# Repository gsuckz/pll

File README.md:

# Sintetizador de Frecuencias en banda Ku 

## Funcionamiento
    El dispositivo genera una señal en banda Ku {10,6 , 11,8} GHz. Con un paso de 1Mhz, teniendo 1200 Valores posibles. Estos se envían a través de una aplicacion de Android usando Bluetooth. También es posible realizar un barrido de frecuecnias, con un paso menor, 0,25 MHz.

Este repositorio contiene el código para controlar un Sintentizador de frecuencias Zarlink SP5769 que controla un VCO HMC534LP5.

La dirección I2C del SP5769 se selecciona con el nivel del tension aplicado a ADDRESS (%Vcc) ADDRESS = "11000101"

El ESP32 debe escribir en los registros del SP5769 los valores (a través de un bus I2C). Los registros son:
## Programmable divider: 
    Controla la razón entre la frecuencia del VCO interno y la de referencia (Un numero de 15 bit)
## Control Data: Tiene varios bits que controlan el funcionamiento (Ver datasheet para saber posicion):

    [R3:R0]: Controla el divisor de frecuencia de referencia (Ver tabla) - Ajustado al valor 64 -> 0101

    [C1:C0]: Seleccion la corriente de la bomba de carga. Ver tabla datasheet (Valor fijado por el circuito)

    RE: Enable del oscilador de ref 

    [T2:T0] = Bits de control de modo test - No se usa

    [P3:P0] = Estados del puerto de salida - No se usa

    RS: REF/COMP seleccion (Se usa alta impedancia)

Aquí se configura: Modo Test Off, Corriente de la bomba de carga Icp=+-155[µA], pin
de REF/COMP en alta impedancia, y todos los puertos, P3 a P0 a 0[V]

## Especifaciones del programa 
### Iniciar 
    El programa debe iniciar la comunicación por bluetooth y configurar el registro de control según se indica en el documento "INFORME-TRABAJO-GRADUACION-CANGEMI-JOSE-I.pdf". Luego debe esperar por cualquiera de las 2 instrucciones posibles.

### Ajuste de frecuencia
    El programa debe recibir por bluetooth el valor de la frecuncia deseada, luego debe calcular el valor del multiplicador necesario y escribirlo en los registros programmable divider.

### Barrido de frecuencia
    El programa de barrer las frecuencias sintetizables en un tiempo indicado por el usuario. Con limites Tmin y Tmax

El valor recibido es una cadena de caracteres con la frecuencia

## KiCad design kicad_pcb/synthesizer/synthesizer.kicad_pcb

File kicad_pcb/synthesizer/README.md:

# Sintetizador

- Transistor BCW31 : [datasheet_BCW31](https://www.alldatasheet.es/datasheet-pdf/view/16150/PHILIPS/BCW31.html)
- Conector SMA Chasis: [Datasheet_Sma](https://www.snapeda.com/parts/CONSMA006.062-G/TE%20Connectivity/datasheet/)

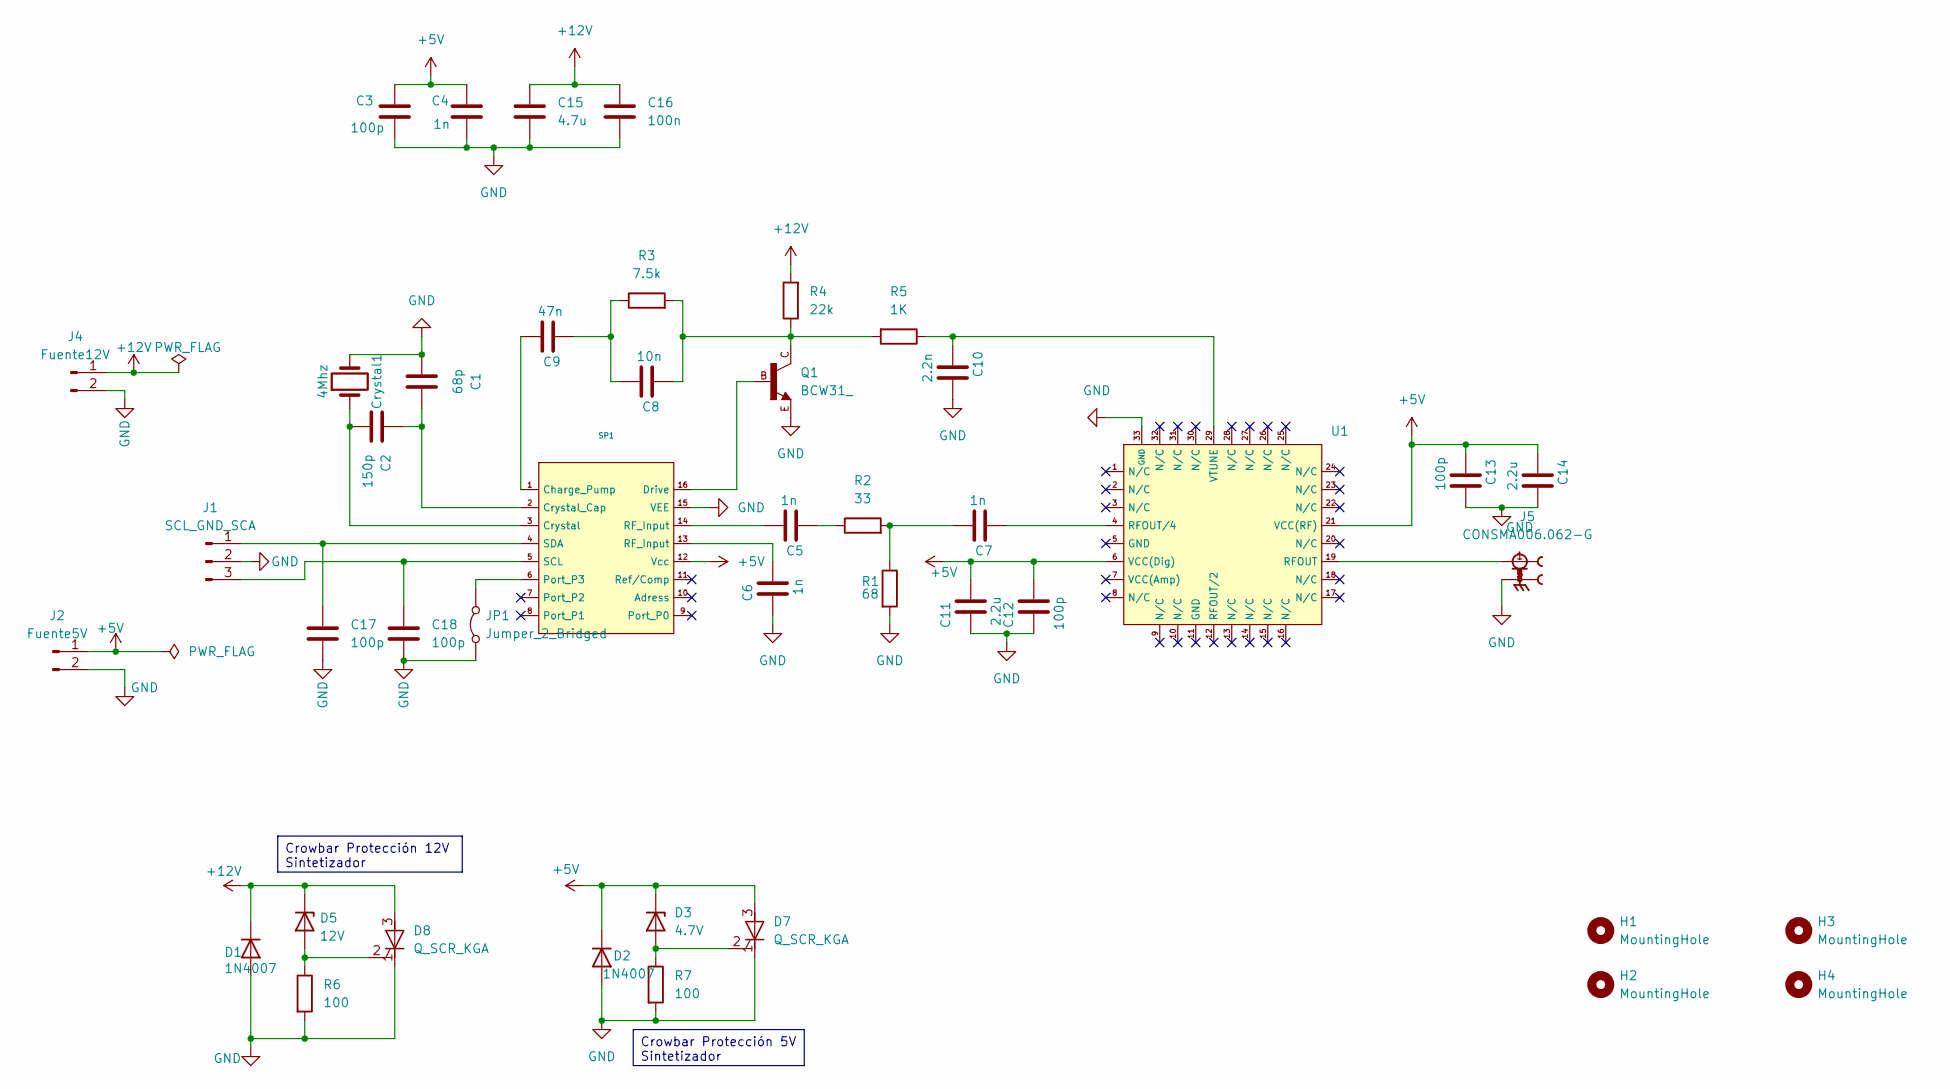
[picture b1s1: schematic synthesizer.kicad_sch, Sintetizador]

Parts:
C1: 68p; C_0805_2012Metric_Pad1.18x1.45mm_HandSolder
C2: 150p; C_0805_2012Metric_Pad1.18x1.45mm_HandSolder
C3, C12, C13, C17, C18: 100p; C_0805_2012Metric_Pad1.18x1.45mm_HandSolder
C4, C5, C6, C7: 1n; C_0805_2012Metric_Pad1.18x1.45mm_HandSolder
C8: 10n; C_0805_2012Metric_Pad1.18x1.45mm_HandSolder
C9: 47n; C_0805_2012Metric_Pad1.18x1.45mm_HandSolder
C10: 2.2n; C_0805_2012Metric_Pad1.18x1.45mm_HandSolder
C11, C14: 2.2u; C_0805_2012Metric_Pad1.18x1.45mm_HandSolder
C15: 4.7u; CP_Radial_D8.0mm_P3.80mm
C16: 100n; C_0805_2012Metric_Pad1.18x1.45mm_HandSolder
Crystal1: 4Mhz; Crystal_HC18-U_Vertical
D1, D2: 1N4007; D_DO-41_SOD81_P10.16mm_Horizontal
D3: 4.7V; D_DO-41_SOD81_P10.16mm_Horizontal
D5: 12V; D_DO-41_SOD81_P10.16mm_Horizontal
D7: Q_SCR_KGA; TO-92_Wide
D8: Q_SCR_KGA; TO-92L_Wide
H1, H2, H3, H4: MountingHole; MountingHole_3.2mm_M3
J1: SCL_GND_SCA; PinHeader_1x03_P2.54mm_Vertical
J2: Fuente5V; PinHeader_1x02_P2.54mm_Vertical
J4: Fuente12V; PinHeader_1x02_P2.54mm_Vertical
J5: CONSMA006.062-G; TE_CONSMA006.062-G; PARTREV B
JP1: Jumper_2_Bridged; PinHeader_1x02_P2.54mm_Vertical
Q1: BCW31_; SOT23-BEC
R1: 68; R_0805_2012Metric_Pad1.20x1.40mm_HandSolder
R2: 33; R_0805_2012Metric_Pad1.20x1.40mm_HandSolder
R3: 7.5k; R_0805_2012Metric_Pad1.20x1.40mm_HandSolder
R4: 22k; R_0805_2012Metric_Pad1.20x1.40mm_HandSolder
R5: 1K; R_0805_2012Metric_Pad1.20x1.40mm_HandSolder
R6, R7: 100; R_Axial_DIN0207_L6.3mm_D2.5mm_P10.16mm_Horizontal
SP1: SOP-16_4.4x10.4mm_P1.27mm
U1: QFN50P500X500X100-33N

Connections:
+5V: C3.1, C4.1, C11.2, C12.2, C13.1, C14.1, D2.1 (K), D3.1 (K), D7.3 (A), J2.1, SP1.12 (Vcc), U1.6 (VCC(Dig)), U1.21 (VCC(RF))
+12V: C15.1, C16.1, D1.1 (K), D5.1 (K), D8.3 (A), J4.1, R4.2
GND: C1.1, C3.2, C4.2, C6.1, C10.2, C11.1, C12.1, C13.2, C14.2, C15.2, C16.2, C17.2, C18.2, Crystal1.2, D1.2 (A), D2.2 (A), D7.1 (K), D8.1 (K), J1.2, J2.2, J4.2, J5.2, J5.3, J5.4, J5.5, JP1.1 (A), Q1.E, R1.2, R6.2, R7.2, SP1.15 (VEE), U1.33 (GND)
unnamed: C5.1, R2.1
unnamed: C5.2, SP1.14 (RF_Input)
unnamed: C6.2, SP1.13 (RF_Input)
unnamed: C7.2, R1.1, R2.2
unnamed: C8.1, Q1.C, R3.2, R4.1, R5.2
unnamed: C8.2, C9.1, R3.1
unnamed: D3.2 (A), D7.2 (G), R7.1
unnamed: D5.2 (A), D8.2 (G), R6.1
unnamed: C17.1, J1.1, SP1.4 (SDA)
unnamed: C18.1, J1.3, SP1.5 (SCL)
unnamed: JP1.2 (B), SP1.6 (Port_P3)
unnamed: C9.2, SP1.1 (Charge_Pump)
unnamed: C2.2, Crystal1.1, SP1.3 (Crystal)
unnamed: C1.2, C2.1, SP1.2 (Crystal_Cap)
unnamed: Q1.B, SP1.16 (Drive)
unnamed: J5.1, U1.19 (RFOUT)
unnamed: C7.1, U1.4 (RFOUT/4)
unnamed: C10.1, R5.1, U1.29 (VTUNE)

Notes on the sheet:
Crowbar Protección 5V Sintetizador
Crowbar Protección 12V Sintetizador

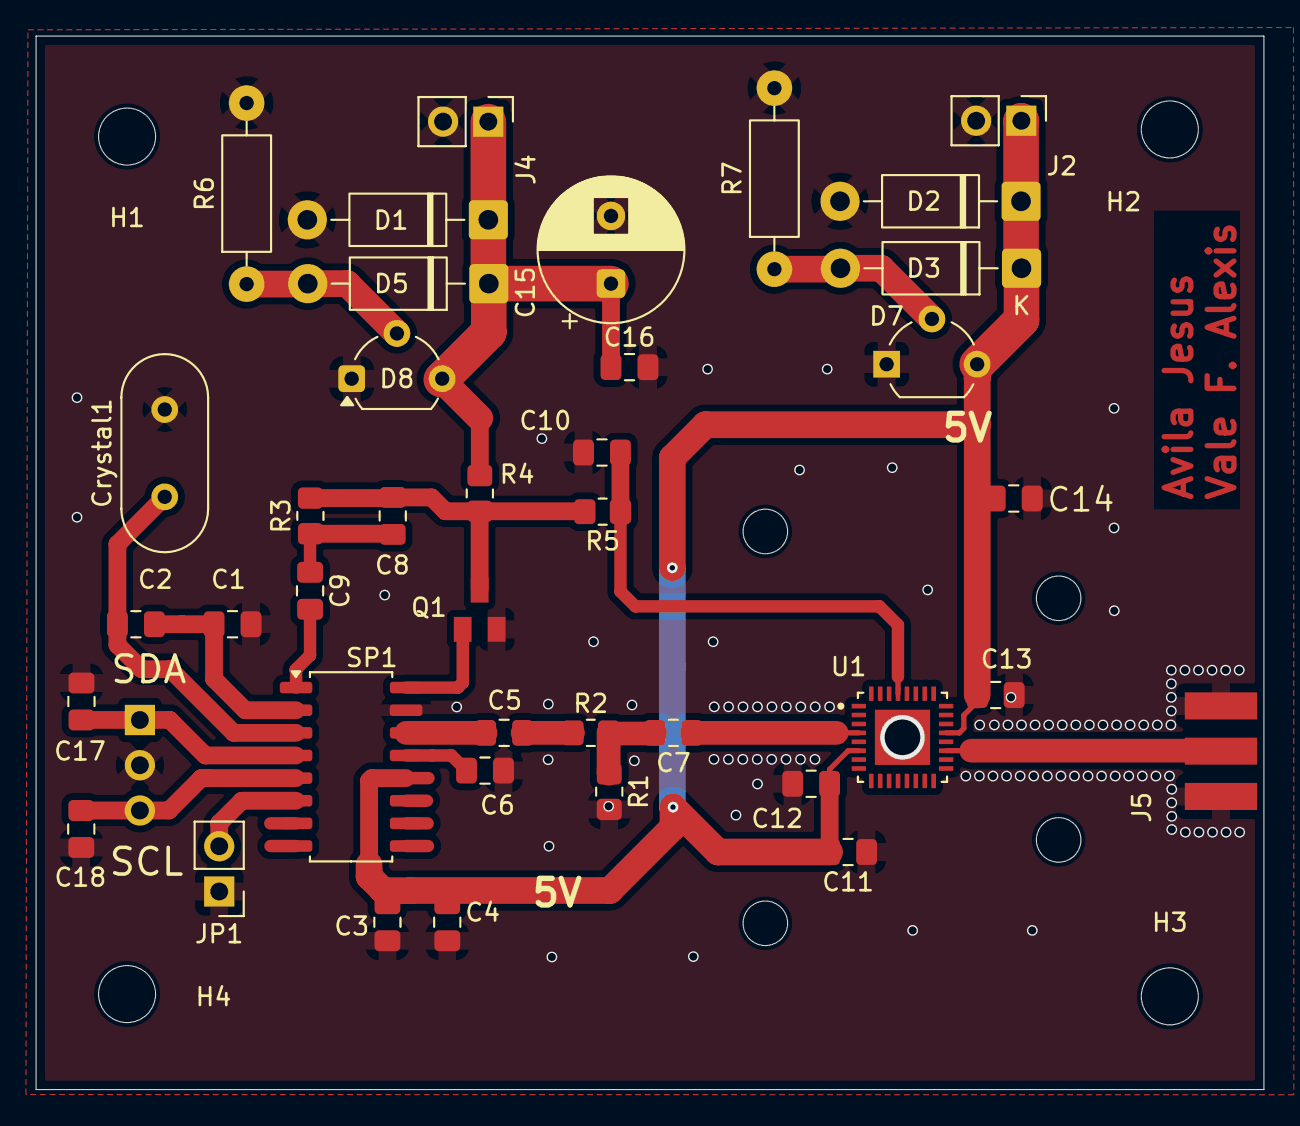
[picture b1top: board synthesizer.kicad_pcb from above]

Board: 2 copper layers, 68.9 x 59.1 mm, 48 parts (1 on the bottom side), 21 nets.

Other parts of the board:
H5, H5#2, H5#3, H5#4: MountingHole; MountingHole_2.5mm

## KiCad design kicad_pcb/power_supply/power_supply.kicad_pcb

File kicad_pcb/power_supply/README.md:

## Datasheet Componentes
- VCO HMC534LP5: [Datasheet](https://www.analog.com/media/en/technical-documentation/data-sheets/hmc534.pdf)

- Sintetizador SP5769: [Datasheet](https://www.alldatasheet.com/datasheet-pdf/view/77217/MITEL/SP5769.html)

- Diodo Zener 1N4732A (4.7V): [Datasheet](https://www.alldatasheet.com/datasheet-pdf/view/58834/DIODES/1N4733A.html) 

- Diodo Zener BZX55C12 (12V): [Datasheet](https://www.vishay.com/docs/85604/bzx55.pdf)

- Tiristor MCR100-6 : [Dataset](https://www.alldatasheet.com/datasheet-pdf/view/888541/SEMTECH_ELEC/MCR100-6.html)

- Tiristor TYN615 (SCR): [Datasheet](https://www.alldatasheet.es/datasheet-pdf/view/25111/STMICROELECTRONICS/TYN612.html)

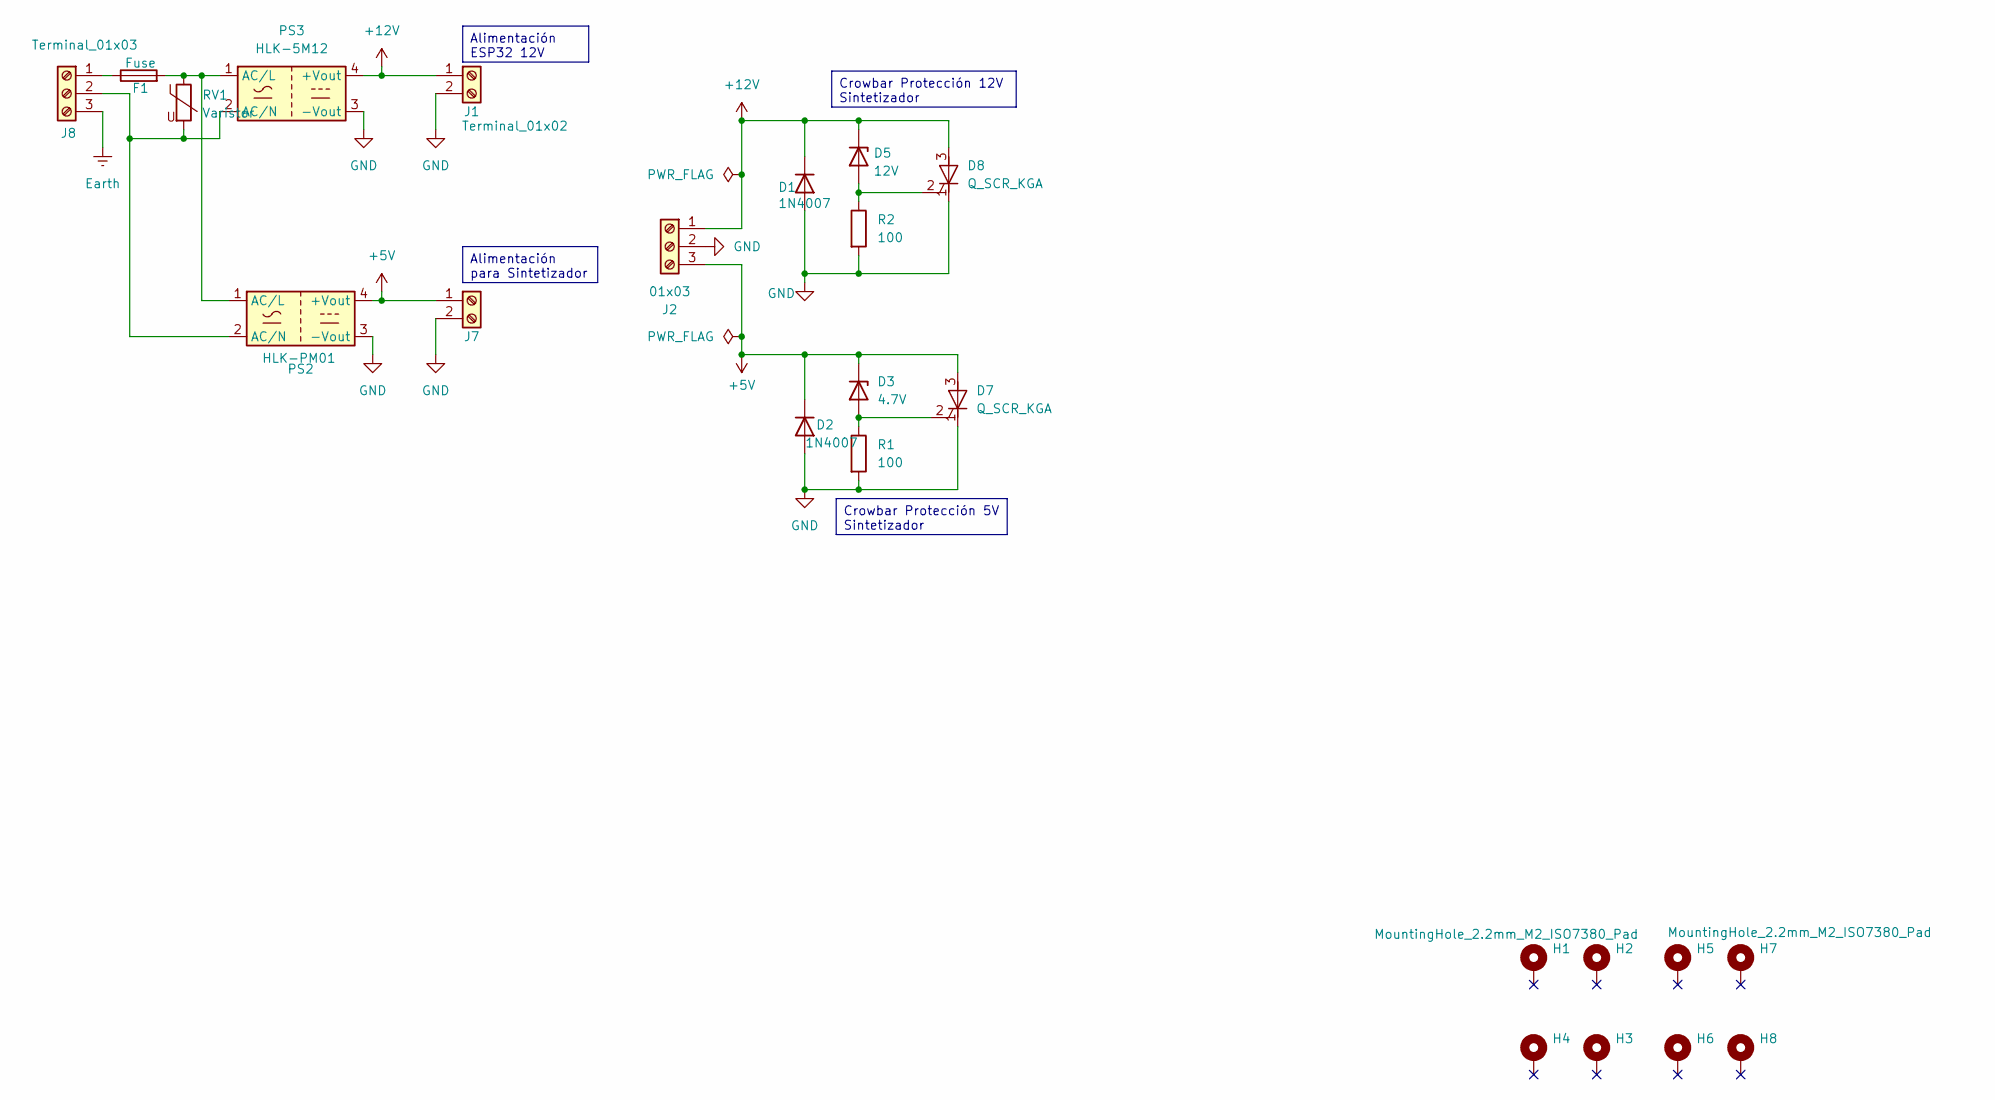
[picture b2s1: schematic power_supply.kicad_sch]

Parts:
D1, D2: 1N4007; D_DO-41_SOD81_P10.16mm_Horizontal
D3: 4.7V; D_DO-41_SOD81_P10.16mm_Horizontal
D5: 12V; D_DO-41_SOD81_P10.16mm_Horizontal
D7: Q_SCR_KGA; TO-92_Wide
D8: Q_SCR_KGA; TO-92L_Wide
F1: Fuse; Fuseholder_Cylinder-5x20mm_Schurter_0031_8201_Horizontal_Op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
H1, H2, H3, H4, H5, H6, H7, H8: MountingHole_2.2mm_M2_ISO7380_Pad
J1, J7: Terminal_01x02; TerminalBlock_MetzConnect_Type011_RT05502HBLC_1x02_P5.00mm_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
J2: 01x03; TerminalBlock_MaiXu_MX126-5.0-03P_1x03_P5.00mm
J8: Terminal_01x03; TerminalBlock_MaiXu_MX126-5.0-03P_1x03_P5.00mm
PS2: HLK-PM01; Converter_ACDC_Hi-Link_HLK-PMxx
PS3: HLK-5M12; Converter_ACDC_Hi-Link_HLK-5Mxx
R1, R2: 100; R_Axial_DIN0207_L6.3mm_D2.5mm_P10.16mm_Horizontal
RV1: Varistor; RV_Disc_D12mm_W4.2mm_P7.5mm

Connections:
+5V: D2.1 (K), D3.1 (K), D7.3 (A), J2.3, J7.1, PS2.4 (+Vout)
+12V: D1.1 (K), D5.1 (K), D8.3 (A), J1.1, J2.1, PS3.4 (+Vout)
Earth: J8.3
GND: D1.2 (A), D2.2 (A), D7.1 (K), D8.1 (K), J1.2, J2.2, J7.2, PS2.3 (-Vout), PS3.3 (-Vout), R1.2, R2.2
unnamed: D3.2 (A), D7.2 (G), R1.1
unnamed: D5.2 (A), D8.2 (G), R2.1
unnamed: F1.1, J8.1
unnamed: J8.2, PS2.2 (AC/N), PS3.2 (AC/N), RV1.2
unnamed: F1.2, PS2.1 (AC/L), PS3.1 (AC/L), RV1.1

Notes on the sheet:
Crowbar Protección 5V Sintetizador
Alimentación para Sintetizador
Crowbar Protección 12V Sintetizador
Alimentación ESP32 12V

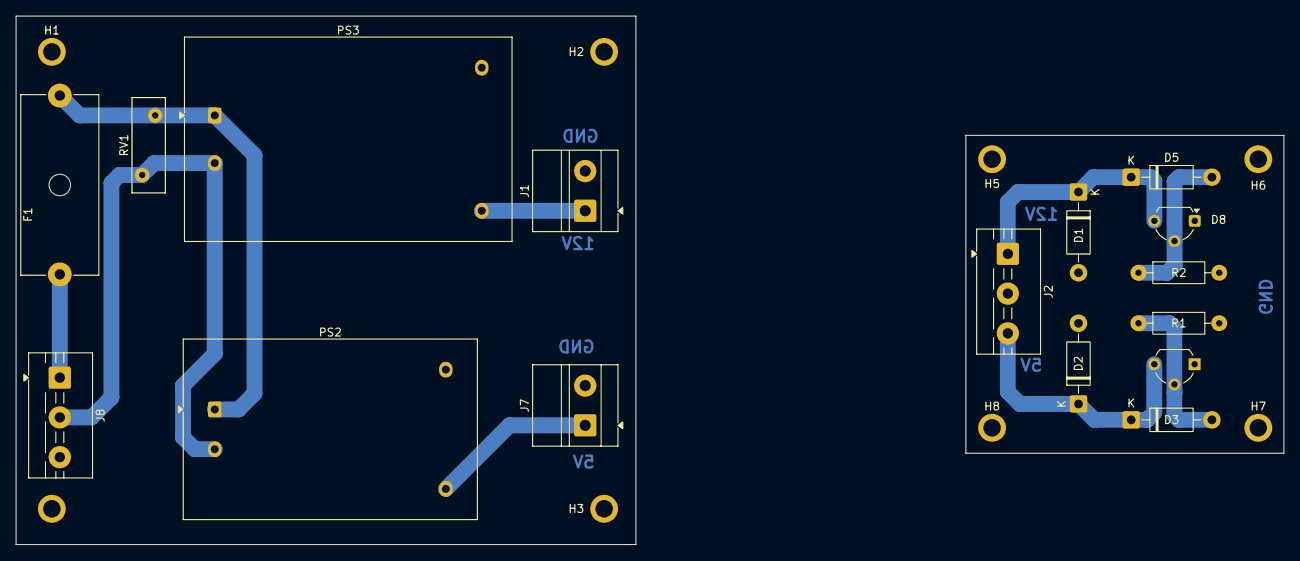
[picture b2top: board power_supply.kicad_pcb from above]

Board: 2 copper layers, 159.5 x 66.5 mm, 24 parts (1 on the bottom side), 8 nets.

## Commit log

2024-08-19 Primer commit
2024-08-19 Actualizado Readme
2024-08-23 Prueba placa OK
2024-08-23 Especificaciones
2024-08-26 COMANDOS FUNCIONA
2024-08-26 Cambios parciales
2024-08-28 Errores de com
2024-08-29 Corregida direccion i2c
2024-10-23 Cambio de valor de R
2024-10-30 agregados test
2024-10-30 agregados msj de test
2024-11-01 nueva modificacion en las divisiones, se agregaron tablas, los divisires estaban mal configurados
2024-11-28 Agregado Display y botones (probar)
2024-11-28 cambios
2025-04-01 Agregado Menu Alexis
2025-04-15 Filtro Botones
2025-04-16 Filtro Anda
2025-05-09 Cambiobot
2025-05-10 Configuración de clangformat. Documentación en buffer
2025-05-10 Separacion Modulo Sint
2025-05-21 App BT anda
2025-06-04 Agregado Barre nfunciona
2025-06-05 Agregado Comando barrer
2025-06-06 SintetizadorTick
2025-06-10 TareaPeriodica
2025-06-12 agregadorBuffer
2025-06-17 AgregadoBarrido2
2025-06-18 Cambios para Tarea
2025-06-18 cambiosprof
2025-06-24 limpieza de codigo sint
2025-06-24 Corregido problema de lock
2025-08-22 NuevaInt
2025-08-22 Pantalla Funciona
2025-08-28 intTeclado
2025-09-01 UI teclado
2025-09-25 Agregadas Sim AWR
2025-09-25 Sim AdapZ SP5769ds
2025-09-27 Agregado Esquema fuente
2025-09-27 Se agrega esquema y pcb de sintetizador
2025-10-01 Agregada LineaPCB
2025-10-02 modificación de pcb y esquema
2025-10-08 Agregadas vias (sin check)
2025-10-14 Simulacion pcb
2025-10-14 cambio de huella y posiciones de elemenntos. se reduce el tamaño de placa
2025-10-14 Se agregan caps para sda y scl
2025-10-14 Cambio de huella R4
2025-10-15 Lineas SDA/SCL
2025-10-15 Se modificaron los tamaños de los elementos smd a 0805 y se modificaron anchos de pistas
2025-10-20 carpeta out
2026-03-17 Cambio de huella
2026-03-28 Se modifica placa para nuevo integrado
2026-04-27 Consulta estado contínuamente y no solo la primera vez
2026-04-28 agreegada app
2026-04-28 comando sintetizador
